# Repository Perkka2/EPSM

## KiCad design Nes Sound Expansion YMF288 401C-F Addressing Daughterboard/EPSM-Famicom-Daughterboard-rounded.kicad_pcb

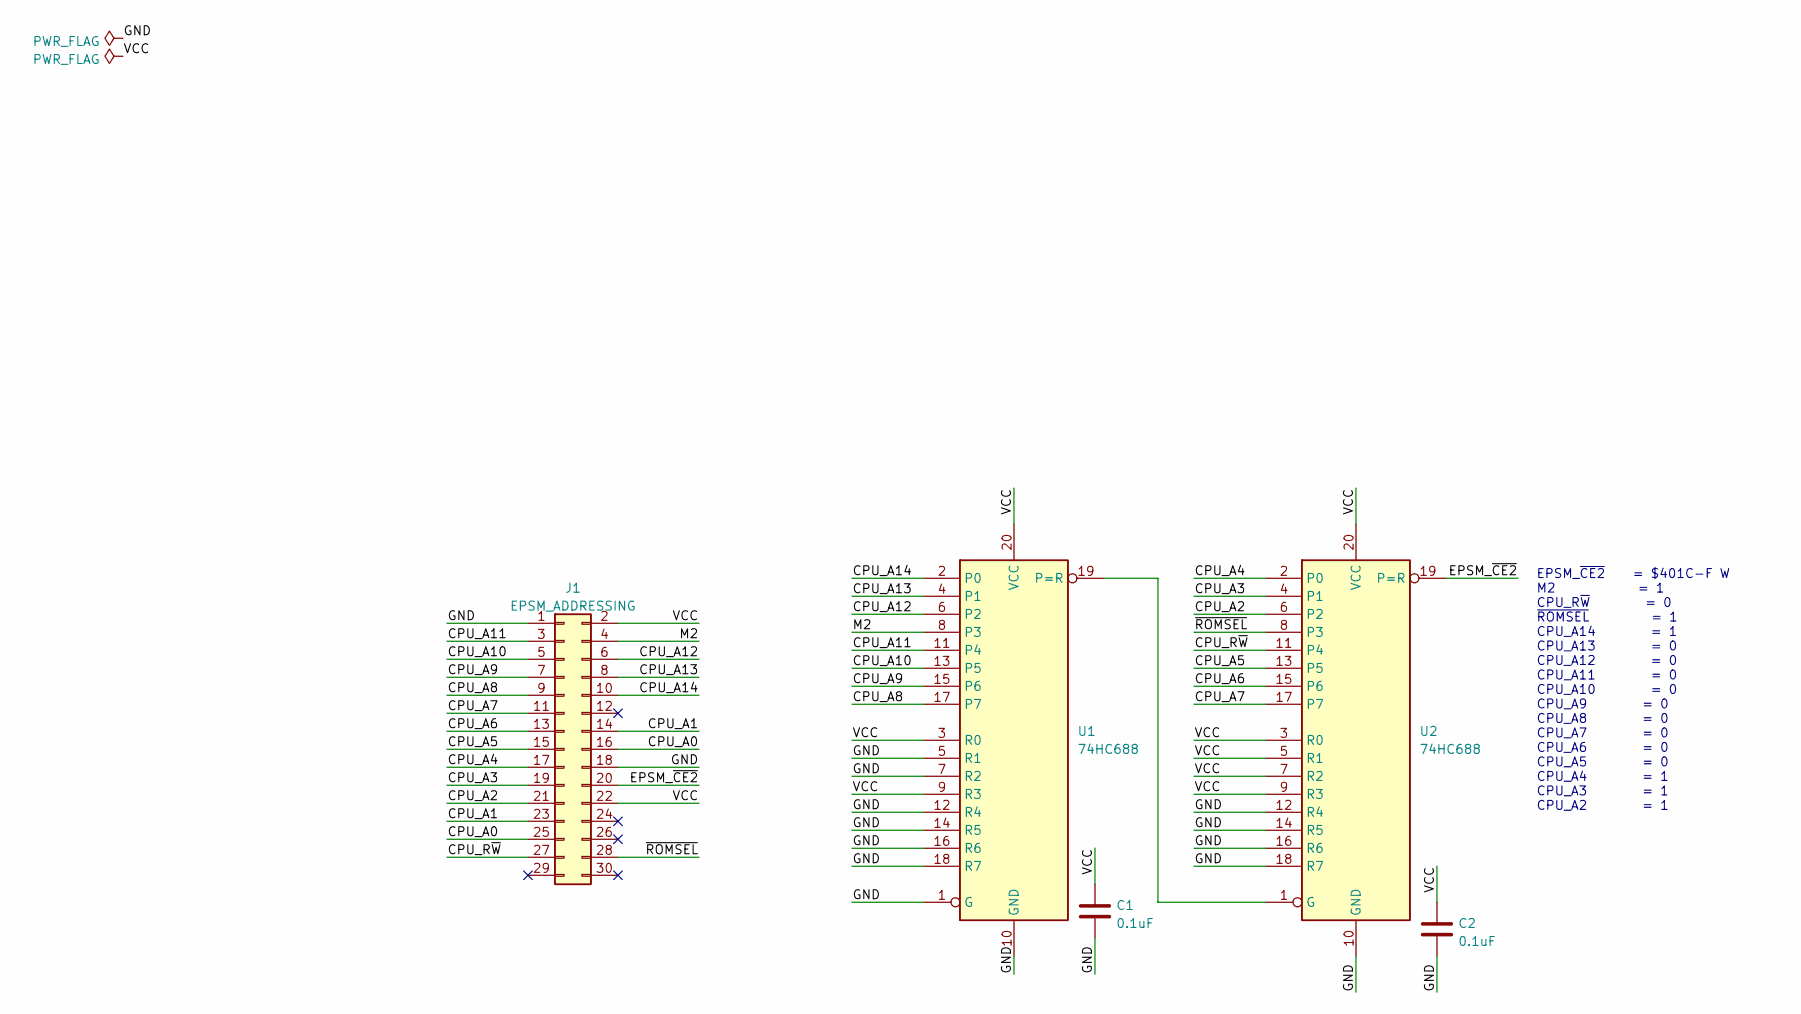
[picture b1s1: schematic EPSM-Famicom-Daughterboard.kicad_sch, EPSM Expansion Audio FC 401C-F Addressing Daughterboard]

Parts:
C1, C2: 0.1uF; C_0805_2012Metric_Pad1.18x1.45mm_HandSolder
J1: EPSM_ADDRESSING; PinHeader_2x15_P2.54mm_Vertical
U1, U2: 74HC688; SOIC-20W_7.5x12.8mm_P1.27mm

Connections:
/CPU_A0: J1.16, J1.25
/CPU_A1: J1.14, J1.23
/CPU_A2: J1.21, U2.6 (P2)
/CPU_A3: J1.19, U2.4 (P1)
/CPU_A4: J1.17, U2.2 (P0)
/CPU_A5: J1.15, U2.13 (P5)
/CPU_A6: J1.13, U2.15 (P6)
/CPU_A7: J1.11, U2.17 (P7)
/CPU_A8: J1.9, U1.17 (P7)
/CPU_A9: J1.7, U1.15 (P6)
/CPU_A10: J1.5, U1.13 (P5)
/CPU_A11: J1.3, U1.11 (P4)
/CPU_A12: J1.6, U1.6 (P2)
/CPU_A13: J1.8, U1.4 (P1)
/CPU_A14: J1.10, U1.2 (P0)
/CPU_R~W: J1.27, U2.11 (P4)
/EPSM_~CE2: J1.20, U2.19 (P=R)
/GND: C1.1, C2.1, J1.1, J1.18, U1.1 (G), U1.5 (R1), U1.7 (R2), U1.10 (GND), U1.12 (R4), U1.14 (R5), U1.16 (R6), U1.18 (R7), U2.10 (GND), U2.12 (R4), U2.14 (R5), U2.16 (R6), U2.18 (R7)
/M2: J1.4, U1.8 (P3)
/VCC: C1.2, C2.2, J1.2, J1.22, U1.3 (R0), U1.9 (R3), U1.20 (VCC), U2.3 (R0), U2.5 (R1), U2.7 (R2), U2.9 (R3), U2.20 (VCC)
/~ROMSEL: J1.28, U2.8 (P3)
unnamed: U1.19 (P=R), U2.1 (G)

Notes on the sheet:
EPSM_~{CE2} = $401C-F W M2 = 1 CPU_R~{W} = 0 ~{ROMSEL} = 1 CPU_A14 = 1 CPU_A13 = 0 CPU_A12 = 0 CPU_A11 = 0 CPU_A10 = 0 CPU_A9 = 0 CPU_A8 = 0 CPU_A7 = 0 CPU_A6 = 0 CPU_A5 = 0 CPU_A4 = 1 CPU_A3 = 1 CPU_A2 = 1

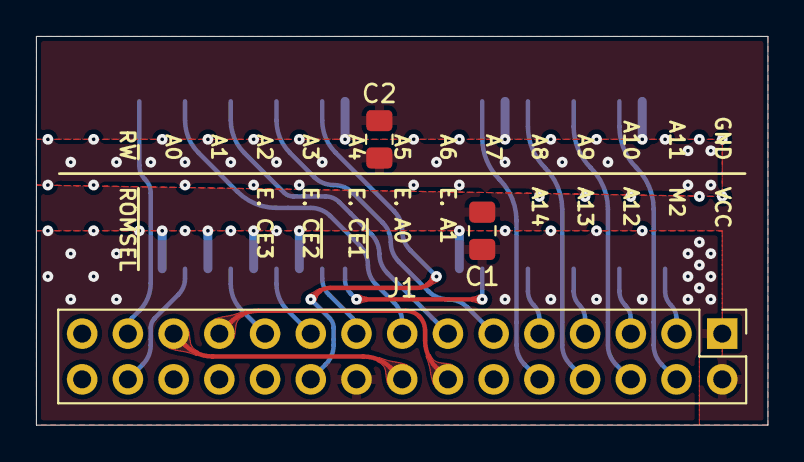
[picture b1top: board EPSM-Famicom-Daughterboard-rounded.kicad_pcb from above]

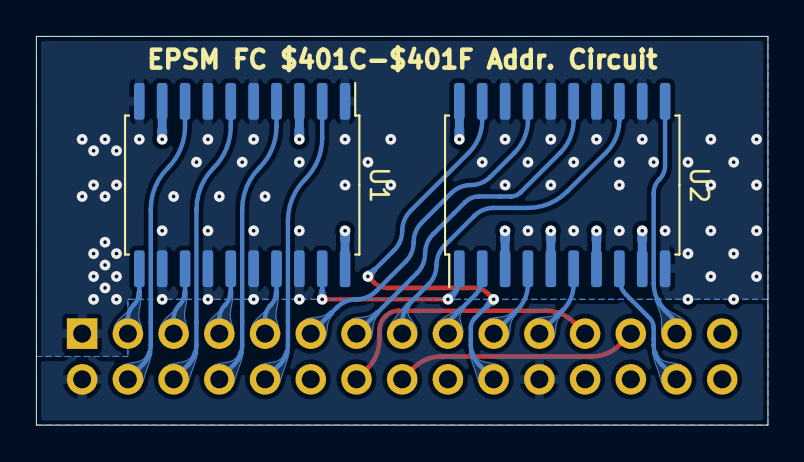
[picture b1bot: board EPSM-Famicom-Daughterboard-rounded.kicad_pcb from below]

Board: 2 copper layers, 40.6 x 21.6 mm, 5 parts (2 on the bottom side), 22 nets.

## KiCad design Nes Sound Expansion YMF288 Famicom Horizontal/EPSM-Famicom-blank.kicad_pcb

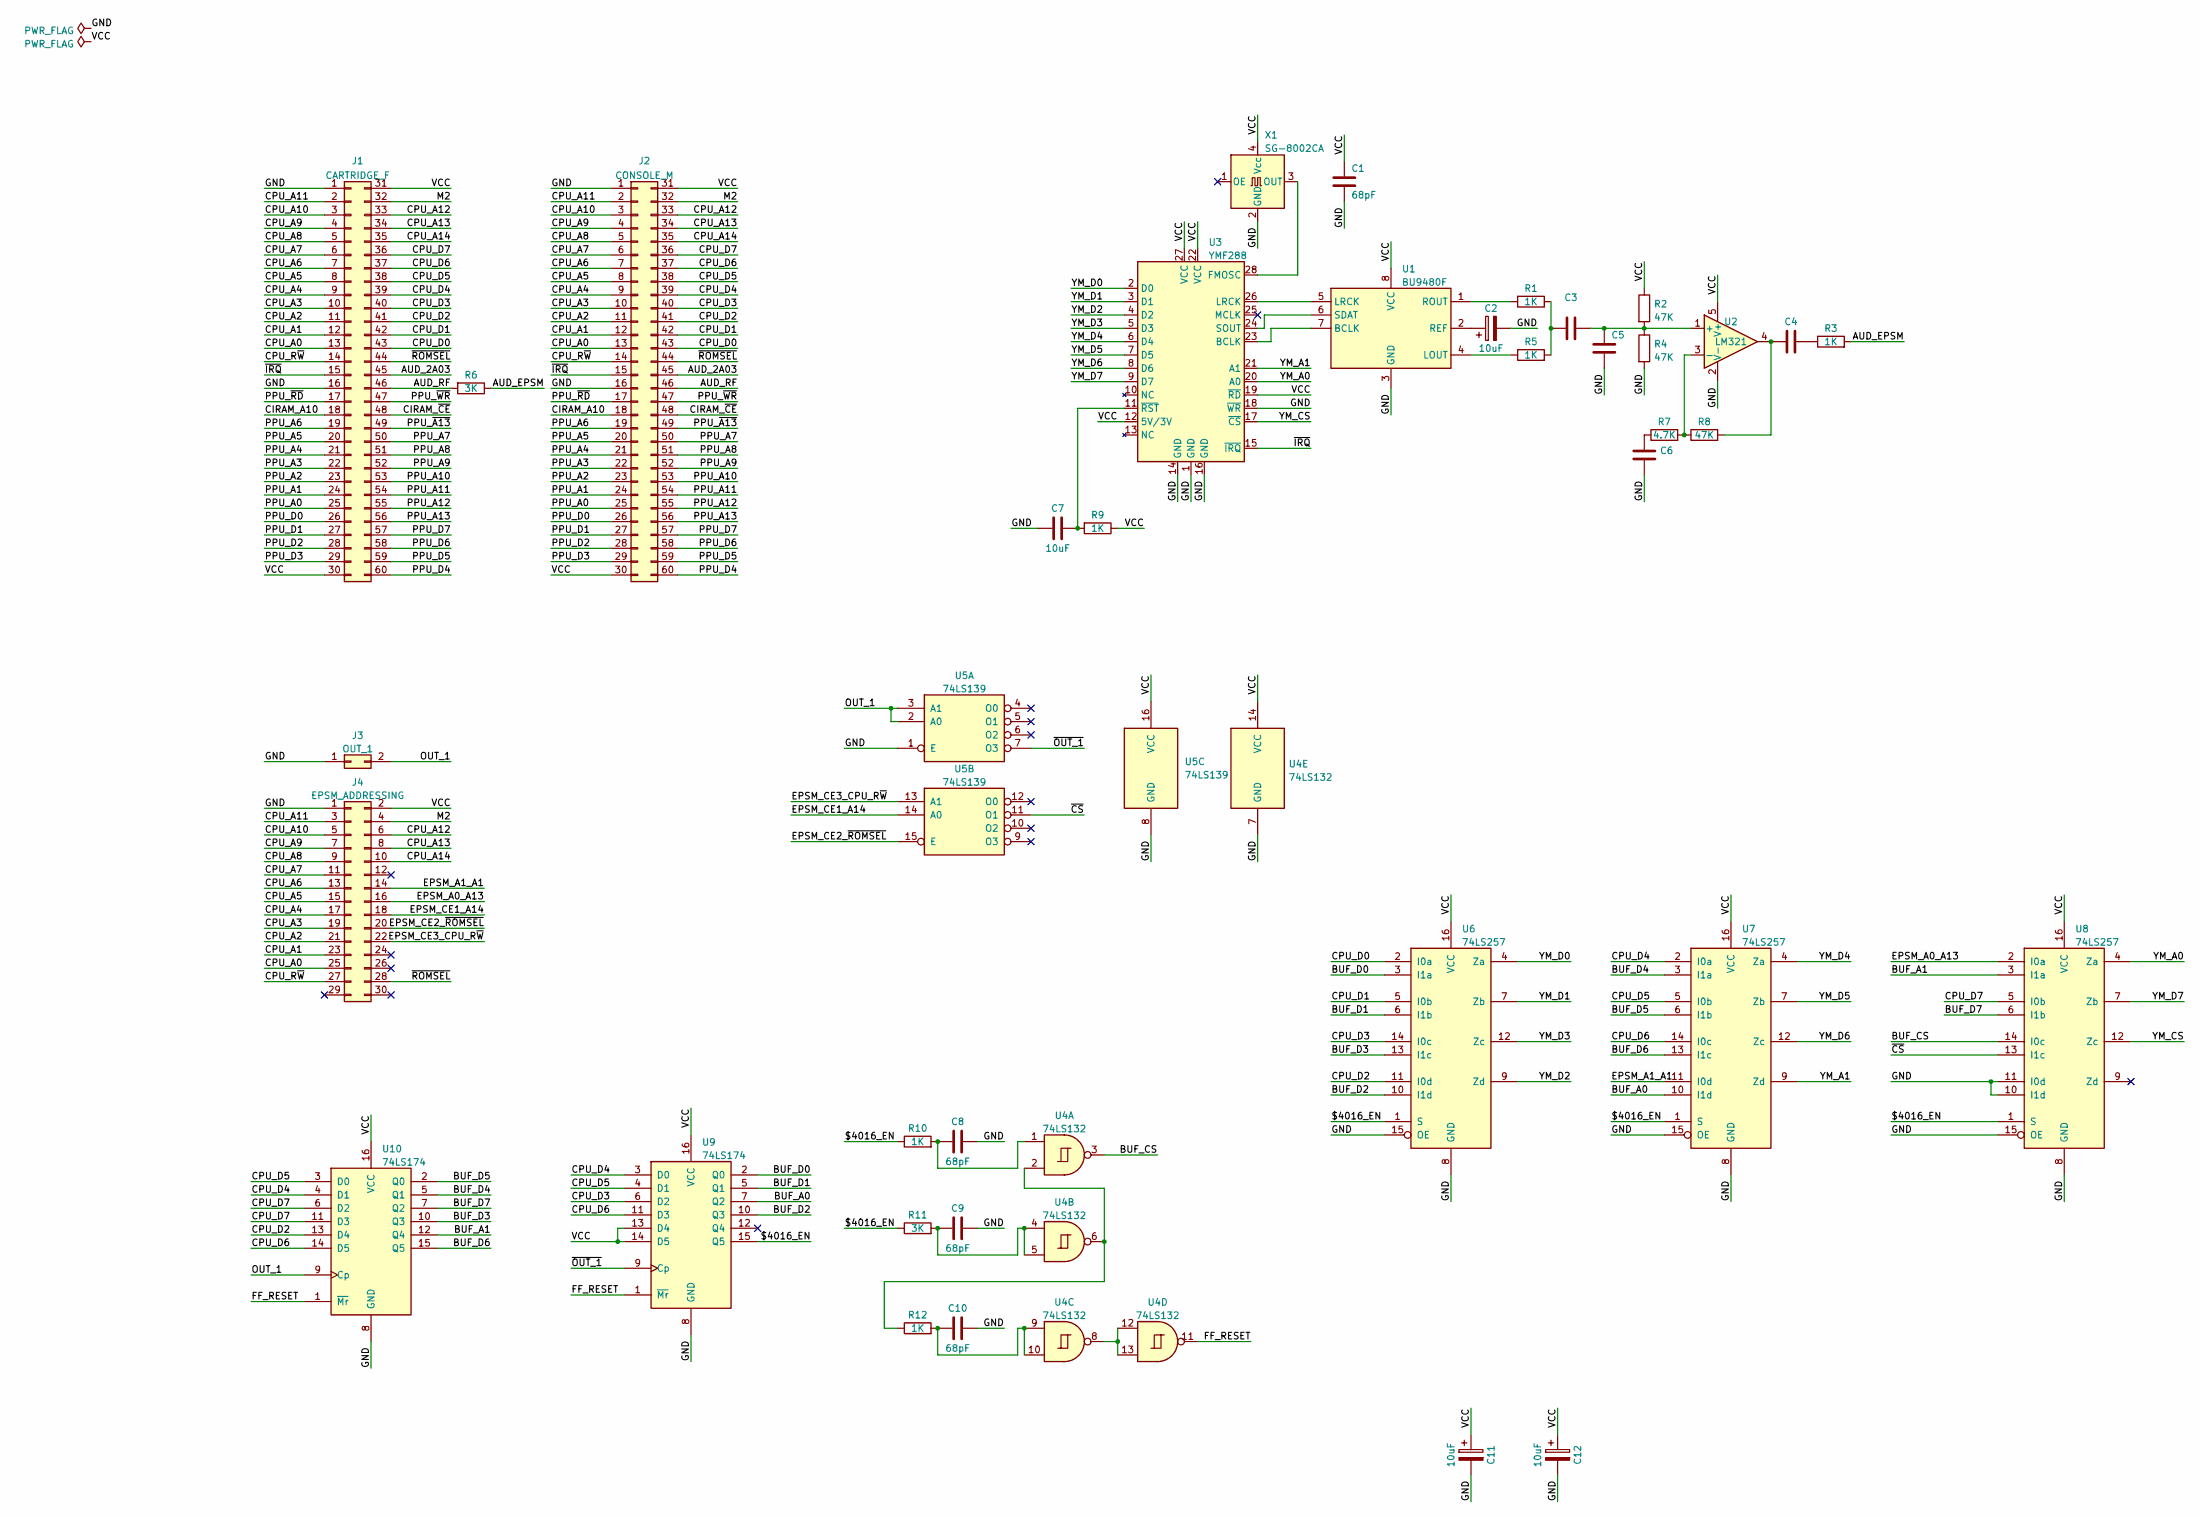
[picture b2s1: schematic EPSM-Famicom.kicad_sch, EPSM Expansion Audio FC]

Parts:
C1, C8, C9, C10: 68pF; C_0805_2012Metric_Pad1.18x1.45mm_HandSolder
C2, C11, C12: 10uF; CP_Elec_4x5.3
C3, C4, C5, C6: (no value)
C7: 10uF
J1: CARTRIDGE_F; FC_CONN_F
J2: CONSOLE_M; HVC-ETROM-01
J3: OUT_1; PinHeader_1x02_P2.54mm_Vertical
J4: EPSM_ADDRESSING; PinSocket_2x15_P2.54mm_Vertical_SMD
R1, R3, R5, R9, R10, R12: 1K; R_0805_2012Metric_Pad1.20x1.40mm_HandSolder
R2, R4, R8: 47K; R_0805_2012Metric_Pad1.20x1.40mm_HandSolder
R6, R11: 3K; R_0805_2012Metric_Pad1.20x1.40mm_HandSolder
R7: 4.7K; R_0805_2012Metric_Pad1.20x1.40mm_HandSolder
U1: BU9480F; SOIC-8_5.275x5.275mm_P1.27mm
U2: LM321; SOT-23-5
U3: YMF288; SOP-28_7.5x12.8mm_P1.27mm
U4: 74LS132; SOIC-14_3.9x8.7mm_P1.27mm
U5: 74LS139; SOIC-16_3.9x9.9mm_P1.27mm
U6, U7, U8: 74LS257; SOIC-16_3.9x9.9mm_P1.27mm
U9, U10: 74LS174; SOIC-16_3.9x9.9mm_P1.27mm
X1: SG-8002CA; Oscillator_SMD_SeikoEpson_SG8002CA-4Pin_7.0x5.0mm

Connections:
/$4016_EN: R10.1, R11.1, U6.1 (S), U7.1 (S), U8.1 (S), U9.15 (Q5)
/AUD_2A03: J1.45, J2.45
/AUD_EPSM: R3.2, R6.1
/AUD_RF: J1.46, J2.46, R6.2
/BUF_A0: U7.10 (I1d), U9.7 (Q2)
/BUF_A1: U8.3 (I1a), U10.12 (Q4)
/BUF_CS: U4.3, U8.14 (I0c)
/BUF_D0: U6.3 (I1a), U9.2 (Q0)
/BUF_D1: U6.6 (I1b), U9.5 (Q1)
/BUF_D2: U6.10 (I1d), U9.10 (Q3)
/BUF_D3: U6.13 (I1c), U10.10 (Q3)
/BUF_D4: U7.3 (I1a), U10.5 (Q1)
/BUF_D5: U7.6 (I1b), U10.2 (Q0)
/BUF_D6: U7.13 (I1c), U10.15 (Q5)
/BUF_D7: U8.6 (I1b), U10.7 (Q2)
/CIRAM_A10: J1.18, J2.18
/CIRAM_~CE: J1.48, J2.48
/CPU_A0: J1.13, J2.13, J4.25
/CPU_A1: J1.12, J2.12, J4.23
/CPU_A2: J1.11, J2.11, J4.21
/CPU_A3: J1.10, J2.10, J4.19
/CPU_A4: J1.9, J2.9, J4.17
/CPU_A5: J1.8, J2.8, J4.15
/CPU_A6: J1.7, J2.7, J4.13
/CPU_A7: J1.6, J2.6, J4.11
/CPU_A8: J1.5, J2.5, J4.9
/CPU_A9: J1.4, J2.4, J4.7
/CPU_A10: J1.3, J2.3, J4.5
/CPU_A11: J1.2, J2.2, J4.3
/CPU_A12: J1.33, J2.33, J4.6
/CPU_A13: J1.34, J2.34, J4.8
/CPU_A14: J1.35, J2.35, J4.10
/CPU_D0: J1.43, J2.43, U6.2 (I0a)
/CPU_D1: J1.42, J2.42, U6.5 (I0b)
/CPU_D2: J1.41, J2.41, U6.11 (I0d), U10.13 (D4)
/CPU_D3: J1.40, J2.40, U6.14 (I0c), U9.6 (D2)
/CPU_D4: J1.39, J2.39, U7.2 (I0a), U9.3 (D0), U10.4 (D1)
/CPU_D5: J1.38, J2.38, U7.5 (I0b), U9.4 (D1), U10.3 (D0)
/CPU_D6: J1.37, J2.37, U7.14 (I0c), U9.11 (D3), U10.14 (D5)
/CPU_D7: J1.36, J2.36, U8.5 (I0b), U10.6 (D2), U10.11 (D3)
/CPU_R~W: J1.14, J2.14, J4.27
/EPSM_A0_A13: J4.16, U8.2 (I0a)
/EPSM_A1_A1: J4.14, U7.11 (I0d)
/EPSM_CE1_A14: J4.18, U5.14 (A0)
/EPSM_CE2_~ROMSEL: J4.20, U5.15 (E)
/EPSM_CE3_CPU_R~W: J4.22, U5.13 (A1)
/FF_RESET: U4.11, U9.1 (~Mr), U10.1 (~Mr)
/GND: C1.2, C2.2, C5.2, C6.2, C7.1, C8.2, C9.2, C10.2, C11.2, C12.2, J1.1, J1.16, J2.1, J2.16, J3.1, J4.1, R4.2, U1.3 (GND), U2.2 (V-), U3.1 (GND), U3.14 (GND), U3.16 (GND), U3.18 (~WR), U4.7 (GND), U5.1 (E), U5.8 (GND), U6.8 (GND), U6.15 (OE), U7.8 (GND), U7.15 (OE), U8.8 (GND), U8.10 (I1d), U8.11 (I0d), U8.15 (OE), U9.8 (GND), U10.8 (GND), X1.2 (GND)
/M2: J1.32, J2.32, J4.4
/OUT_1: J3.2, U5.2 (A0), U5.3 (A1), U10.9 (Cp)
/PPU_A0: J1.25, J2.25
/PPU_A1: J1.24, J2.24
/PPU_A2: J1.23, J2.23
/PPU_A3: J1.22, J2.22
/PPU_A4: J1.21, J2.21
/PPU_A5: J1.20, J2.20
/PPU_A6: J1.19, J2.19
/PPU_A7: J1.50, J2.50
/PPU_A8: J1.51, J2.51
/PPU_A9: J1.52, J2.52
/PPU_A10: J1.53, J2.53
/PPU_A11: J1.54, J2.54
/PPU_A12: J1.55, J2.55
/PPU_A13: J1.56, J2.56
/PPU_D0: J1.26, J2.26
/PPU_D1: J1.27, J2.27
/PPU_D2: J1.28, J2.28
/PPU_D3: J1.29, J2.29
/PPU_D4: J1.60, J2.60
/PPU_D5: J1.59, J2.59
/PPU_D6: J1.58, J2.58
/PPU_D7: J1.57, J2.57
/PPU_~A13: J1.49, J2.49
/PPU_~RD: J1.17, J2.17
/PPU_~WR: J1.47, J2.47
/VCC: C1.1, C11.1, C12.1, J1.30, J1.31, J2.30, J2.31, J4.2, R2.1, R9.1, U1.8 (VCC), U2.5 (V+), U3.12 (5V/3V), U3.19 (~RD), U3.22 (VCC), U3.27 (VCC), U4.14 (VCC), U5.16 (VCC), U6.16 (VCC), U7.16 (VCC), U8.16 (VCC), U9.13 (D4), U9.14 (D5), U9.16 (VCC), U10.16 (VCC), X1.4 (Vcc)
/YM_A0: U3.20 (A0), U8.4 (Za)
/YM_A1: U3.21 (A1), U7.9 (Zd)
/YM_CS: U3.17 (~CS), U8.12 (Zc)
/YM_D0: U3.2 (D0), U6.4 (Za)
/YM_D1: U3.3 (D1), U6.7 (Zb)
/YM_D2: U3.4 (D2), U6.9 (Zd)
/YM_D3: U3.5 (D3), U6.12 (Zc)
/YM_D4: U3.6 (D4), U7.4 (Za)
/YM_D5: U3.7 (D5), U7.7 (Zb)
/YM_D6: U3.8 (D6), U7.12 (Zc)
/YM_D7: U3.9 (D7), U8.7 (Zb)
/~CS: U5.11 (O1), U8.13 (I1c)
/~IRQ: J1.15, J2.15, U3.15 (~IRQ)
/~OUT_1: U5.7 (O3), U9.9 (Cp)
/~ROMSEL: J1.44, J2.44, J4.28
unnamed: C2.1, U1.2 (REF)
unnamed: C3.1, R1.1, R5.2
unnamed: C3.2, C5.1, R2.2, R4.1, U2.1 (+)
unnamed: C4.1, R8.2, U2.4
unnamed: C4.2, R3.1
unnamed: C6.1, R7.1
unnamed: C7.2, R9.2, U3.11 (~RST)
unnamed: C8.1, R10.2, U4.1
unnamed: C9.1, R11.2, U4.4, U4.5
unnamed: C10.1, R12.2, U4.9, U4.10
unnamed: R1.2, U1.1 (ROUT)
unnamed: R5.1, U1.4 (LOUT)
unnamed: R7.2, R8.1, U2.3 (-)
unnamed: R12.1, U4.2, U4.6
unnamed: U1.5 (LRCK), U3.26 (LRCK)
unnamed: U1.6 (SDAT), U3.24 (SOUT)
unnamed: U1.7 (BCLK), U3.23 (BCLK)
unnamed: U3.28 (FMOSC), X1.3 (OUT)
unnamed: U4.8, U4.12, U4.13

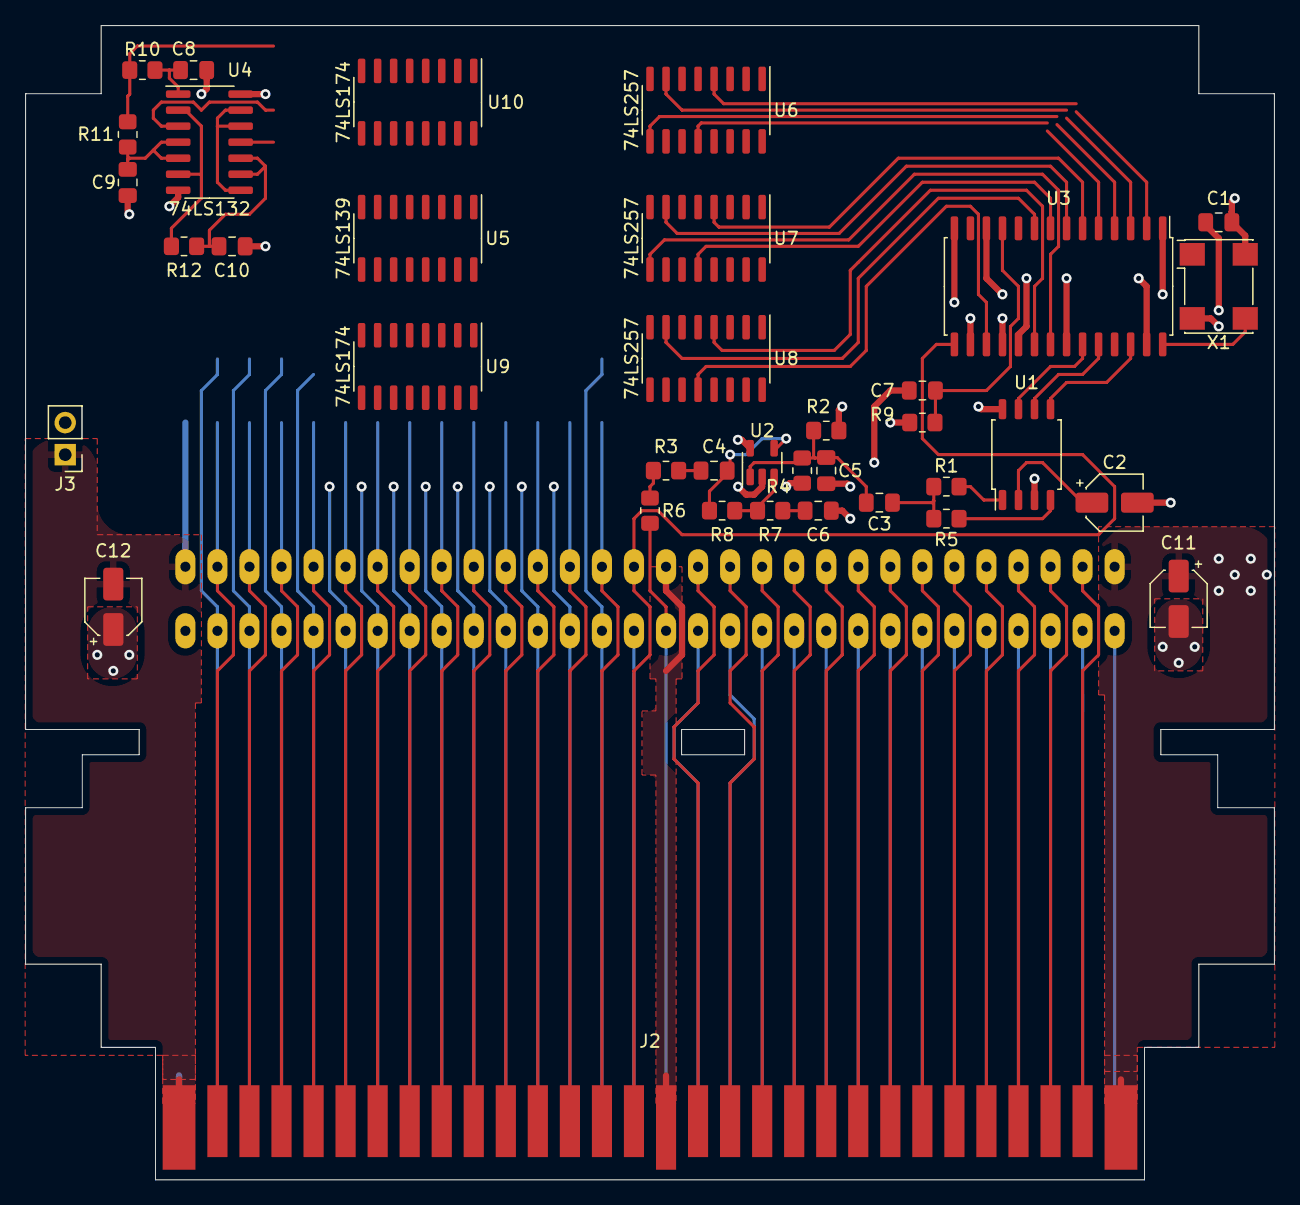
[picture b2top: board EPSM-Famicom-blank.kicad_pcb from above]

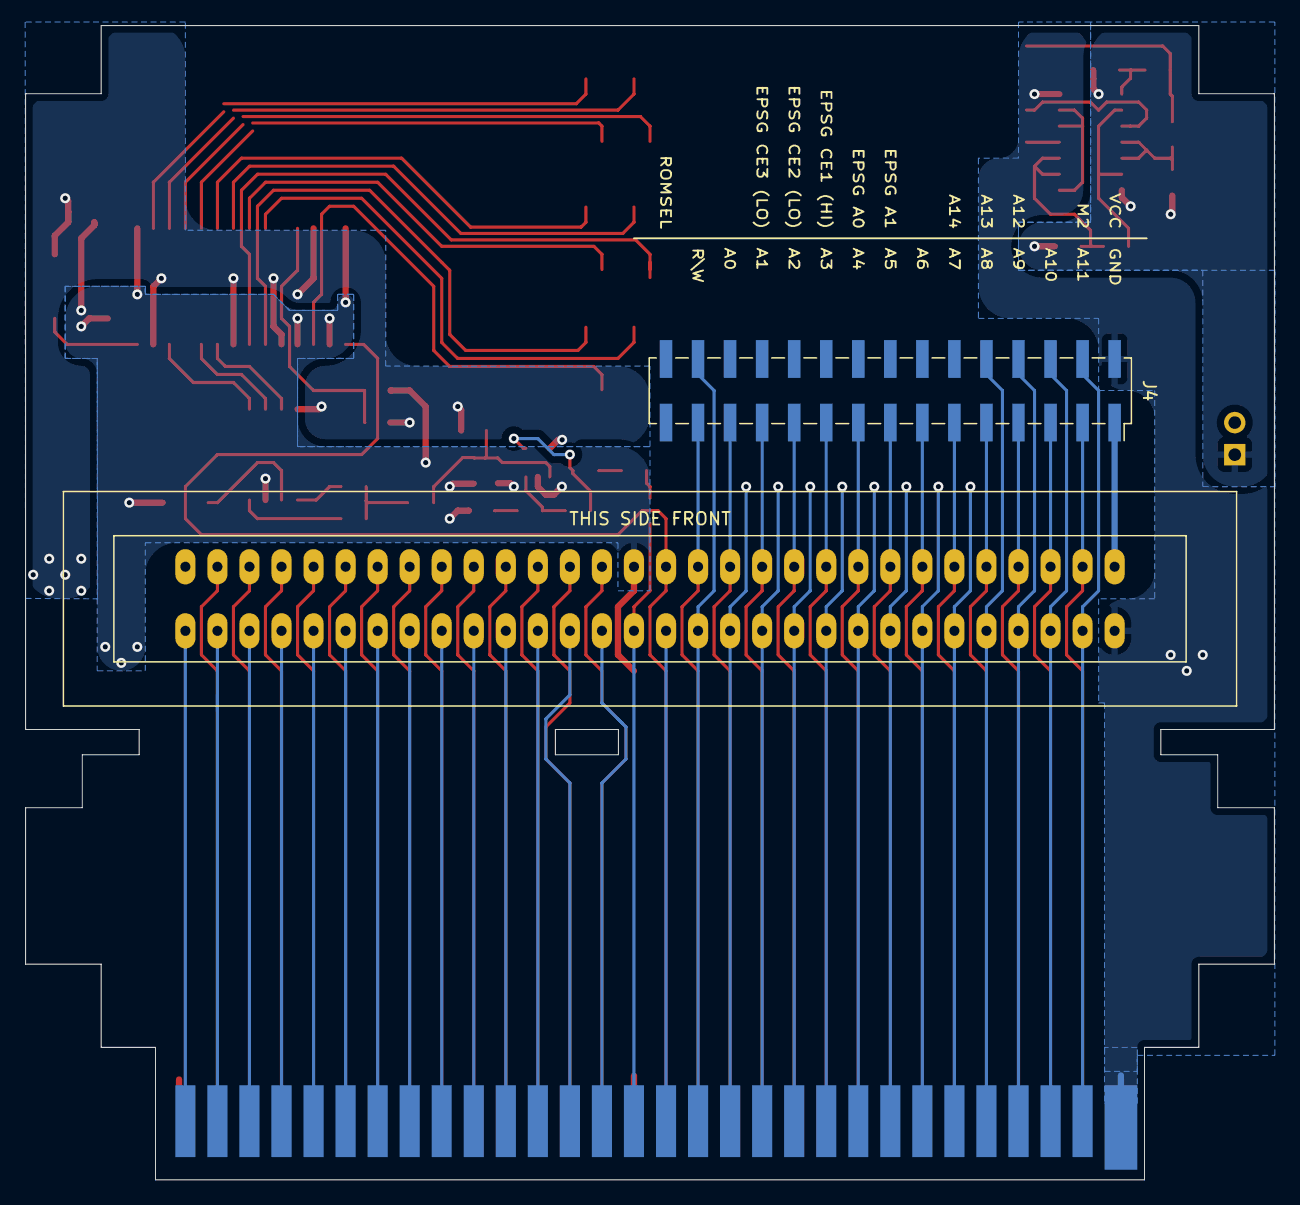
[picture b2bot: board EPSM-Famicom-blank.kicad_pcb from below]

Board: 2 copper layers, 99.0 x 91.5 mm, 39 parts (2 on the bottom side), 110 nets.

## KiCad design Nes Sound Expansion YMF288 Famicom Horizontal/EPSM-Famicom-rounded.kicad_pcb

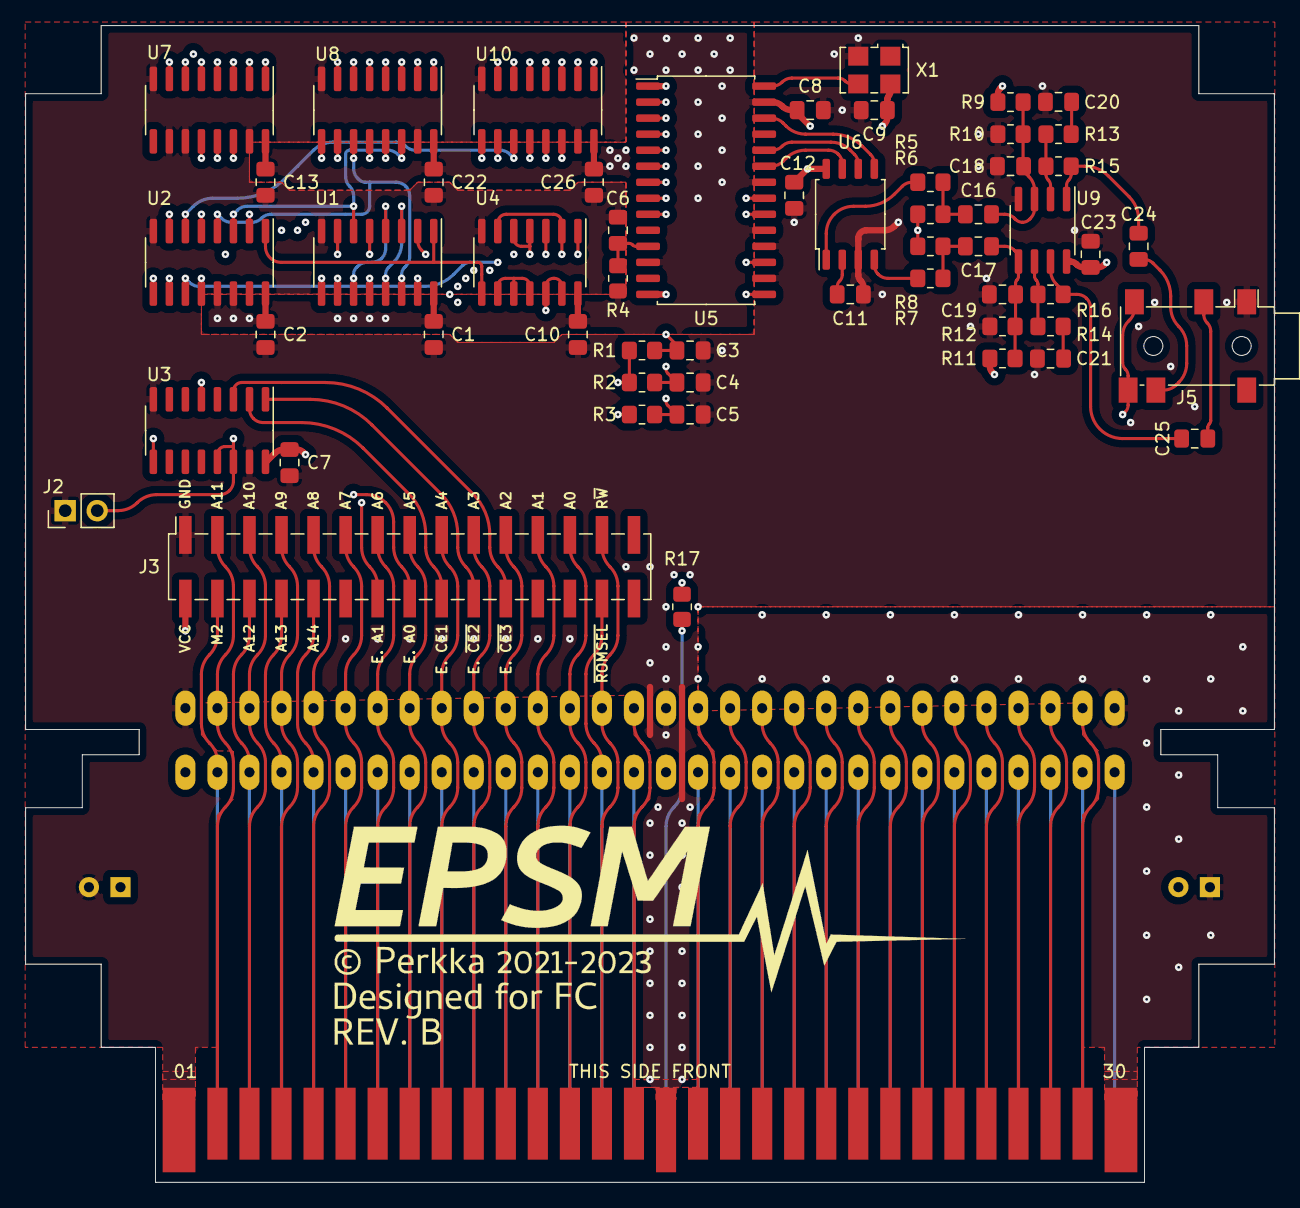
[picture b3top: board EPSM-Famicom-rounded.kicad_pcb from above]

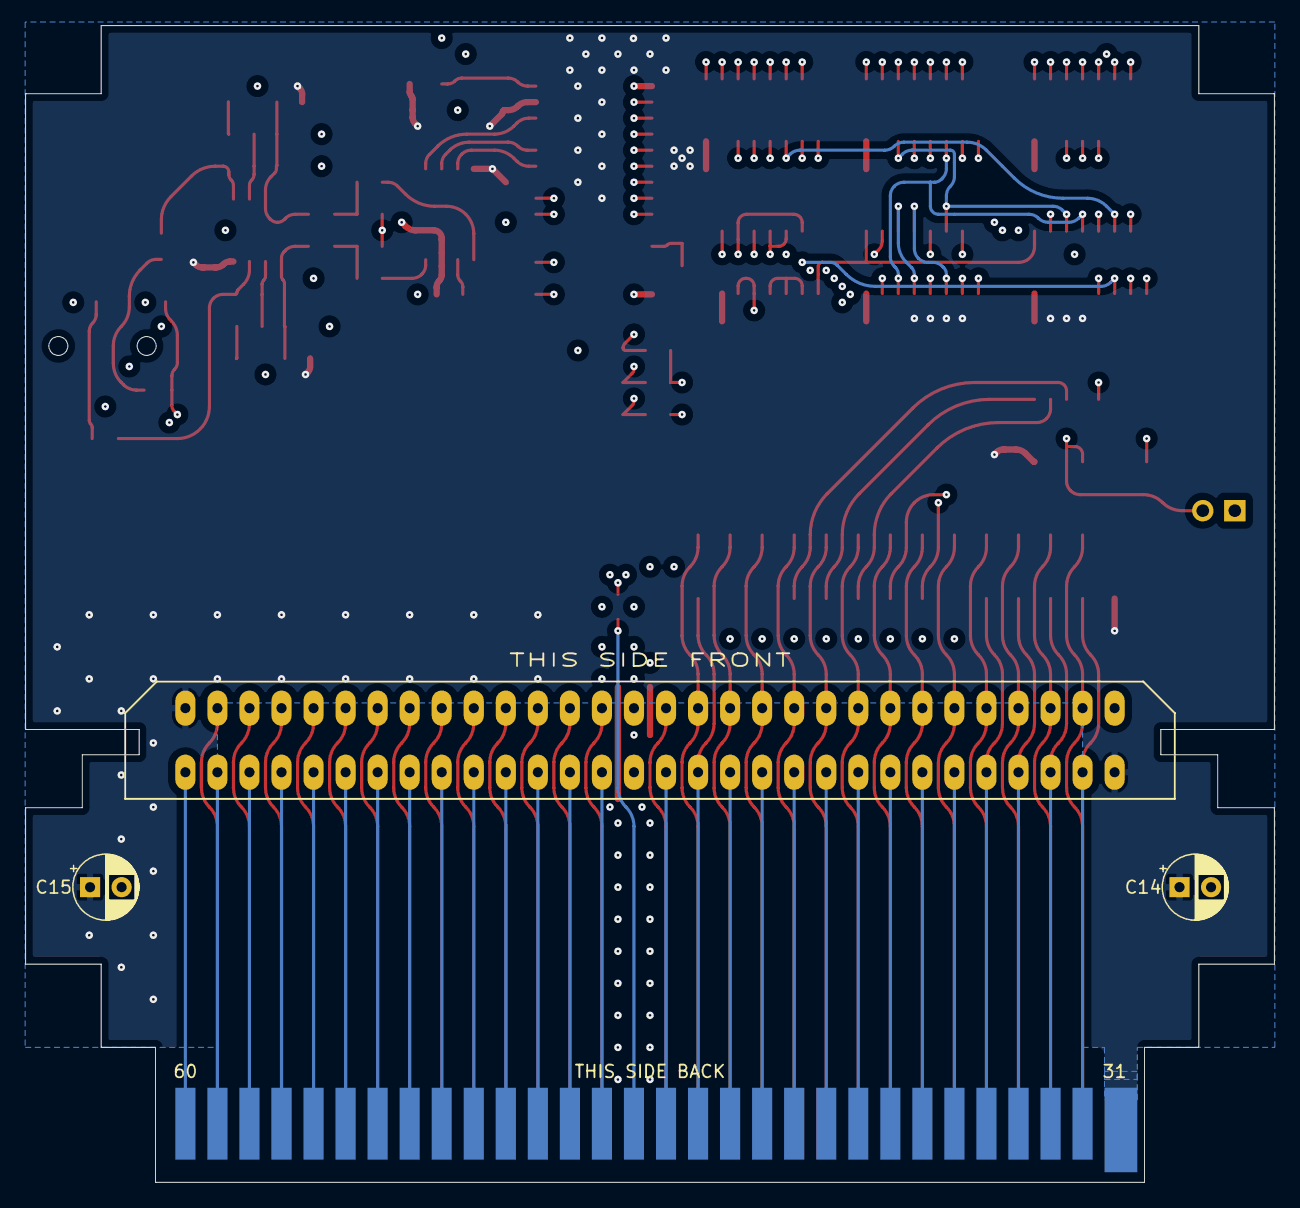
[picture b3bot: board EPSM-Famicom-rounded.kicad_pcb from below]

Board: 4 copper layers, 99.0 x 91.7 mm, 60 parts (3 on the bottom side), 117 nets.

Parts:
C1, C2, C7, C8, C10, C12, C13, C22, C23, C26: 0.1uF; C_0805_2012Metric_Pad1.18x1.45mm_HandSolder
C3, C4, C5, C9, C18, C19: 68pF; C_0805_2012Metric_Pad1.18x1.45mm_HandSolder
C6, C11, C16, C17, C20, C21, C24, C25: 10uF; C_0805_2012Metric_Pad1.18x1.45mm_HandSolder
C14, C15: 100uF; CP_Radial_D5.0mm_P2.50mm
J1: CARTRIDGE_F; FC_CONN_F
J2: OUT_1; PinHeader_1x02_P2.54mm_Vertical
J3: EPSM_ADDRESSING; PinSocket_2x15_P2.54mm_Vertical_SMD
J4: CONSOLE_M; HVC-ETROM-01
J5: AudioJack4_SwitchTR1; Jack_3.5mm_PJ311_Horizontal
R1, R3, R4, R17: 1K; R_0805_2012Metric_Pad1.20x1.40mm_HandSolder
R2, R6, R8: 3K; R_0805_2012Metric_Pad1.20x1.40mm_HandSolder
R5, R7: 680; R_0805_2012Metric_Pad1.20x1.40mm_HandSolder
R9, R10, R11, R12: 47K; R_0805_2012Metric_Pad1.20x1.40mm_HandSolder
R13, R14: 8.2K; R_0805_2012Metric_Pad1.20x1.40mm_HandSolder
R15, R16: 22K; R_0805_2012Metric_Pad1.20x1.40mm_HandSolder
Ref**: Val**; EPSM_silkscreen
U1, U2: 74LS174; SOIC-16_3.9x9.9mm_P1.27mm
U3: 74LS139; SOIC-16_3.9x9.9mm_P1.27mm
U4: 74LS132; SOIC-14_3.9x8.7mm_P1.27mm
U5: YMF288; SOP-28_7.5x12.8mm_P1.27mm
U6: BU9480F; SOIC-8_5.275x5.275mm_P1.27mm
U7, U8, U10: 74LS257; SOIC-16_3.9x9.9mm_P1.27mm
U9: LM358; SOIC-8_3.9x4.9mm_P1.27mm
X1: SG-8002CA; Oscillator_SMD_SeikoEpson_SG8002LB-4Pin_5.0x3.2mm

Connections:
/$4016_EN: R1.1, R2.1, U2.12 (Q4), U7.1 (S), U8.1 (S), U10.1 (S)
/AUD_2A03: J1.45, J4.45
/AUD_EPSM: J4.46, R17.2
/AUD_RF: J1.46, R6.2, R8.2
/BUF_A0: U2.7 (Q2), U7.3 (I1a)
/BUF_A1: U2.10 (Q3), U7.6 (I1b)
/BUF_CS: U4.3, U7.14 (I0c)
/BUF_D0: U1.2 (Q0), U10.3 (I1a)
/BUF_D1: U1.5 (Q1), U10.6 (I1b)
/BUF_D2: U1.7 (Q2), U10.13 (I1c)
/BUF_D3: U1.15 (Q5), U10.10 (I1d)
/BUF_D4: U1.12 (Q4), U8.3 (I1a)
/BUF_D5: U1.10 (Q3), U8.6 (I1b)
/BUF_D6: U2.2 (Q0), U8.13 (I1c)
/BUF_D7: U2.5 (Q1), U8.10 (I1d)
/CIRAM_A10: J1.18, J4.18
/CIRAM_~CE: J1.48, J4.48
/CPU_A0: J1.13, J3.25, J4.13
/CPU_A1: J1.12, J3.23, J4.12
/CPU_A2: J1.11, J3.21, J4.11
/CPU_A3: J1.10, J3.19, J4.10
/CPU_A4: J1.9, J3.17, J4.9
/CPU_A5: J1.8, J3.15, J4.8
/CPU_A6: J1.7, J3.13, J4.7
/CPU_A7: J1.6, J3.11, J4.6
/CPU_A8: J1.5, J3.9, J4.5
/CPU_A9: J1.4, J3.7, J4.4
/CPU_A10: J1.3, J3.5, J4.3
/CPU_A11: J1.2, J3.3, J4.2
/CPU_A12: J1.33, J3.6, J4.33
/CPU_A13: J1.34, J3.8, J4.34
/CPU_A14: J1.35, J3.10, J4.35
/CPU_D0: J1.43, J4.43, U10.2 (I0a)
/CPU_D1: J1.42, J4.42, U10.5 (I0b)
/CPU_D2: J1.41, J4.41, U2.11 (D3), U10.14 (I0c)
/CPU_D3: J1.40, J4.40, U2.6 (D2), U10.11 (I0d)
/CPU_D4: J1.39, J4.39, U1.3 (D0), U1.13 (D4), U8.2 (I0a)
/CPU_D5: J1.38, J4.38, U1.4 (D1), U1.11 (D3), U8.5 (I0b)
/CPU_D6: J1.37, J4.37, U1.6 (D2), U2.3 (D0), U8.14 (I0c)
/CPU_D7: J1.36, J4.36, U1.14 (D5), U2.4 (D1), U8.11 (I0d)
/CPU_R~W: J1.14, J3.27, J4.14
/EPSM_A0_A13: J3.16, U7.5 (I0b)
/EPSM_A1_A1: J3.14, U7.2 (I0a)
/EPSM_CE1_A14: J3.18, U3.2 (A0)
/EPSM_CE2_~ROMSEL: J3.20, U3.1 (E)
/EPSM_CE3_CPU_R~W: J3.22, U3.3 (A1)
/FF_RESET: U1.1 (~Mr), U2.1 (~Mr), U4.8
/GND: C1.1, C2.1, C3.2, C4.2, C5.2, C6.1, C7.1, C8.1, C9.2, C10.1, C11.2, C12.1, C13.1, C14.2, C15.2, C18.2, C19.2, C20.1, C21.1, C22.1, C23.1, C26.1, J1.1, J1.16, J2.1, J3.1, J4.1, J4.16, J5.S, R10.2, R12.2, U1.8 (GND), U2.8 (GND), U3.8 (GND), U3.15 (E), U4.7 (GND), U5.1 (GND), U5.14 (GND), U5.16 (GND), U5.18 (~WR), U6.3 (GND), U7.8 (GND), U7.10 (I1d), U7.11 (I0d), U7.15 (OE), U8.8 (GND), U8.15 (OE), U9.4 (V-), U10.8 (GND), U10.15 (OE), X1.2 (GND)
/M2: J1.32, J3.4, J4.32
/OUT_1: J2.2, U1.9 (Cp), U3.13 (A1), U3.14 (A0)
/PPU_A0: J1.25, J4.25
/PPU_A1: J1.24, J4.24
/PPU_A2: J1.23, J4.23
/PPU_A3: J1.22, J4.22
/PPU_A4: J1.21, J4.21
/PPU_A5: J1.20, J4.20
/PPU_A6: J1.19, J4.19
/PPU_A7: J1.50, J4.50
/PPU_A8: J1.51, J4.51
/PPU_A9: J1.52, J4.52
/PPU_A10: J1.53, J4.53
/PPU_A11: J1.54, J4.54
/PPU_A12: J1.55, J4.55
/PPU_A13: J1.56, J4.56
/PPU_D0: J1.26, J4.26
/PPU_D1: J1.27, J4.27
/PPU_D2: J1.28, J4.28
/PPU_D3: J1.29, J4.29
/PPU_D4: J1.60, J4.60
/PPU_D5: J1.59, J4.59
/PPU_D6: J1.58, J4.58
/PPU_D7: J1.57, J4.57
/PPU_~A13: J1.49, J4.49
/PPU_~RD: J1.17, J4.17
/PPU_~WR: J1.47, J4.47
/VCC: C1.2, C2.2, C7.2, C8.2, C9.1, C10.2, C12.2, C13.2, C14.1, C15.1, C22.2, C23.2, C26.2, J1.30, J1.31, J3.2, J4.30, J4.31, R4.1, R9.1, R11.1, U1.16 (VCC), U2.13 (D4), U2.14 (D5), U2.16 (VCC), U3.16 (VCC), U4.14 (VCC), U5.12 (5V/3V), U5.19 (~RD), U5.22 (VCC), U5.27 (VCC), U6.8 (VCC), U7.16 (VCC), U8.16 (VCC), U9.8 (V+), U10.16 (VCC), X1.4 (Vcc)
/YM_A0: U5.20 (A0), U7.7 (Zb)
/YM_A1: U5.21 (A1), U7.4 (Za)
/YM_CS: U5.17 (~CS), U7.12 (Zc)
/YM_D0: U5.2 (D0), U10.4 (Za)
/YM_D1: U5.3 (D1), U10.7 (Zb)
/YM_D2: U5.4 (D2), U10.12 (Zc)
/YM_D3: U5.5 (D3), U10.9 (Zd)
/YM_D4: U5.6 (D4), U8.4 (Za)
/YM_D5: U5.7 (D5), U8.7 (Zb)
/YM_D6: U5.8 (D6), U8.12 (Zc)
/YM_D7: U5.9 (D7), U8.9 (Zd)
/~CS: U3.5 (O1), U7.13 (I1c)
/~IRQ: J1.15, J4.15, U5.15 (~IRQ)
/~OUT_1: U2.9 (Cp), U3.9 (O3)
/~ROMSEL: J1.44, J3.28, J4.44
unnamed: C3.1, R1.2, U4.1
unnamed: C4.1, R2.2, U4.4, U4.5
unnamed: C5.1, R3.2, U4.12, U4.13
unnamed: C6.2, R4.2, U5.11 (~RST)
unnamed: C11.1, U6.2 (REF)
unnamed: C16.1, R5.1, R6.1
unnamed: C16.2, C18.1, R9.2, R10.1, U9.3 (+)
unnamed: C17.1, R7.1, R8.1
unnamed: C17.2, C19.1, R11.2, R12.1, U9.5 (+)
unnamed: C20.2, R13.1
unnamed: C21.2, R14.1
unnamed: C24.1, R15.2, U9.1
unnamed: C24.2, J5.T
unnamed: C25.1, R16.2, U9.7
unnamed: C25.2, J5.R1
unnamed: J5.R1N, J5.TN, R17.1
unnamed: R3.1, U4.2, U4.6
unnamed: R5.2, U6.1 (ROUT)
unnamed: R7.2, U6.4 (LOUT)
unnamed: R13.2, R15.1, U9.2 (-)
unnamed: R14.2, R16.1, U9.6 (-)
unnamed: U4.9, U4.10, U4.11
unnamed: U5.23 (BCLK), U6.7 (BCLK)
unnamed: U5.24 (SOUT), U6.6 (SDAT)
unnamed: U5.26 (LRCK), U6.5 (LRCK)
unnamed: U5.28 (FMOSC), X1.3 (OUT)

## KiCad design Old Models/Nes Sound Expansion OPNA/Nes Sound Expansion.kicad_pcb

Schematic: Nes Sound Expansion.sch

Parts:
C1: C; C_Disc_D5.0mm_W2.5mm_P5.00mm
C2: 10uf; CP_Radial_D5.0mm_P2.50mm
C3, C4, C7, C9: 2.2nf; C_Disc_D8.0mm_W2.5mm_P5.00mm
C5: 68p; C_Disc_D8.0mm_W2.5mm_P5.00mm
C6, C8: 2.7nf; C_Disc_D8.0mm_W2.5mm_P5.00mm
C10, C11, C12, C13: 4.7u; CP_Radial_D5.0mm_P2.50mm
D1: 1N4148; D_DO-35_SOD27_P7.62mm_Horizontal
J1: NES-SNES Port1; PinHeader_1x07_P2.54mm_Vertical
J2: NES-SNES Port2; PinHeader_1x07_P2.54mm_Vertical
J3: EXP 1-24; PinHeader_1x24_P2.54mm_Vertical
J4: EXP 25-48; PinHeader_1x24_P2.54mm_Vertical
J5: EN Switch; PinHeader_1x02_P2.54mm_Vertical
J6: AUD Out; PinHeader_1x04_P2.54mm_Vertical
J7: EN LED; PinHeader_1x02_P2.54mm_Vertical
R1, R2, R3, R4: 4.7k; R_Axial_DIN0207_L6.3mm_D2.5mm_P10.16mm_Horizontal
R5, R6, R7, R8: 1k; R_Axial_DIN0207_L6.3mm_D2.5mm_P10.16mm_Horizontal
R9: 330; R_Axial_DIN0207_L6.3mm_D2.5mm_P10.16mm_Horizontal
U1: 74LS139; DIP-16_W7.62mm
U2, U3, U4: RC4558; DIP-8_W7.62mm
X1: CXO_DIP8; Oscillator_DIP-8
YM2608: YM2608; DIP-64_W19.05_P1.78
YM3016: YM3016; DIP-16_W7.62mm

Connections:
+5V: D1.1 (K), J5.1, J7.2, U1.16 (VCC), U2.8 (V+), U3.8 (V+), U4.8 (V+), X1.8 (Vcc), YM2608.28, YM2608.35, YM2608.59, YM2608.62, YM3016.1, YM3016.3, YM3016.6, YM3016.9
Aout_YM2608: C11.1, C12.1, YM2608.27
GND: C1.1, C2.2, C3.1, C4.1, C5.1, C7.1, C9.1, J1.7, J2.7, J3.2, J4.2, J6.1, R9.2, U1.8 (GND), U2.4 (V-), U3.4 (V-), U4.4 (V-), X1.4 (GND), YM2608.1, YM2608.26, YM2608.32, YM2608.39, YM2608.58, YM3016.2
unnamed: C1.2, D1.2 (A), YM2608.33
unnamed: C2.1, U2.3 (+), YM3016.16
unnamed: C3.2, U3.5 (+), YM3016.10
unnamed: C4.2, U3.3 (+), YM3016.11
unnamed: C5.2, U2.5 (+), YM3016.13
unnamed: C6.2, R1.1, R3.2
unnamed: C7.2, R3.1, U4.3 (+)
unnamed: C8.2, R2.1, R4.2
unnamed: C9.2, R4.1, U4.5 (+)
unnamed: C6.1, C10.1, U4.1, U4.2 (-)
unnamed: C10.2, R5.2
unnamed: C11.2, R6.2
unnamed: C12.2, R7.2
unnamed: C8.1, C13.1, U4.6 (-), U4.7
unnamed: C13.2, R8.2
unnamed: J1.1, J2.1, J3.1, J4.1, J5.2
unnamed: J1.2, J4.12
unnamed: J1.3, J2.3, J4.6
unnamed: J1.4, J4.14
unnamed: J2.2, J3.11
unnamed: J2.4, J3.19
unnamed: J3.5, U1.15 (E)
unnamed: J3.7, U1.14 (A0)
unnamed: J3.8, YM2608.60
unnamed: J4.8, U1.13 (A1)
unnamed: J4.11, YM2608.61
unnamed: J4.17, YM2608.2
unnamed: J4.18, YM2608.3
unnamed: J4.19, YM2608.4
unnamed: J4.20, YM2608.5
unnamed: J4.21, YM2608.6
unnamed: J4.22, YM2608.7
unnamed: J4.23, YM2608.8
unnamed: J4.24, YM2608.9
unnamed: J6.3, R5.1, R6.1
unnamed: J6.4, R7.1, R8.1
unnamed: J7.1, R9.1
unnamed: R1.2, U3.1, U3.2 (-)
unnamed: R2.2, U3.6 (-), U3.7
unnamed: U1.11 (O1), YM2608.57
unnamed: U2.1, U2.2 (-), YM3016.14, YM3016.15
unnamed: U2.6 (-), U2.7, YM3016.12
unnamed: X1.5 (OUT), YM2608.63
unnamed: YM2608.29, YM3016.8
unnamed: YM2608.30, YM3016.7
unnamed: YM2608.31, YM3016.4
unnamed: YM2608.64, YM3016.5

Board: 2 copper layers, 37 parts (0 on the bottom side), 50 nets, no tracks yet.
